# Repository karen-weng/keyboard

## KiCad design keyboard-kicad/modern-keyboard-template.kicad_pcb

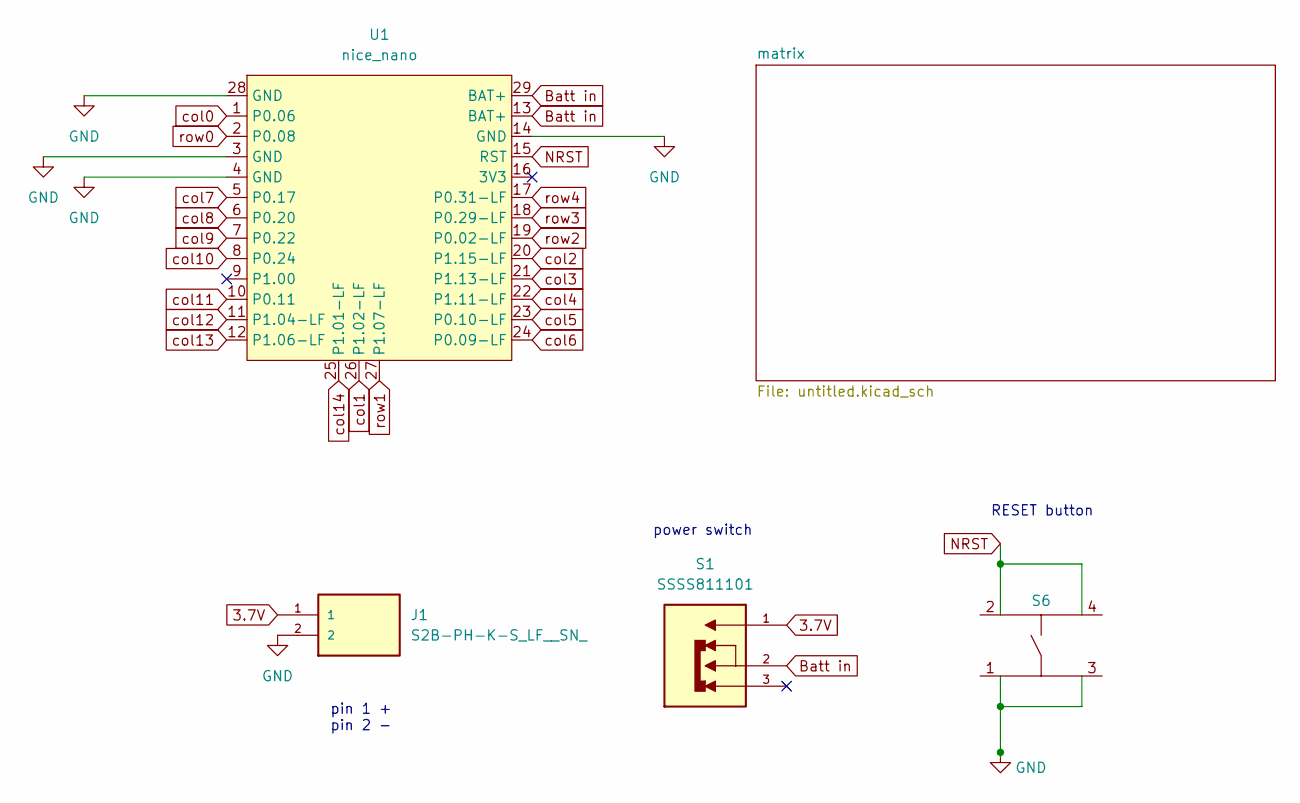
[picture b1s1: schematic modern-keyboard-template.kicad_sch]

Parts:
J1: S2B-PH-K-S_LF__SN_; JST_S2B-PH-K-S_LF__SN_
S1: SSSS811101; SW_SSSS811101; PARTREV N/A
S6: EVQ-PUA02K
U1: nice_nano; nice_nano_AH_USBup

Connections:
3.7V: J1.1, S1.1
Batt in: S1.2, U1.13 (BAT+), U1.29 (BAT+)
GND: J1.2, S6.1, S6.3, U1.3 (GND), U1.4 (GND), U1.14 (GND), U1.28 (GND)
NRST: S6.2, S6.4, U1.15 (RST)
col0: U1.1 (P0.06); also elsewhere on the board
col1: U1.26 (P1.02-LF); also elsewhere on the board
col2: U1.20 (P1.15-LF); also elsewhere on the board
col3: U1.21 (P1.13-LF); also elsewhere on the board
col4: U1.22 (P1.11-LF); also elsewhere on the board
col5: U1.23 (P0.10-LF); also elsewhere on the board
col6: U1.24 (P0.09-LF); also elsewhere on the board
col7: U1.5 (P0.17); also elsewhere on the board
col8: U1.6 (P0.20); also elsewhere on the board
col9: U1.7 (P0.22); also elsewhere on the board
col10: U1.8 (P0.24); also elsewhere on the board
col11: U1.10 (P0.11); also elsewhere on the board
col12: U1.11 (P1.04-LF); also elsewhere on the board
col13: U1.12 (P1.06-LF); also elsewhere on the board
col14: U1.25 (P1.01-LF); also elsewhere on the board
row0: U1.2 (P0.08); also elsewhere on the board
row1: U1.27 (P1.07-LF); also elsewhere on the board
row2: U1.19 (P0.02-LF); also elsewhere on the board
row3: U1.18 (P0.29-LF); also elsewhere on the board
row4: U1.17 (P0.31-LF); also elsewhere on the board

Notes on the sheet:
RESET button
power switch
pin 1 + pin 2 -

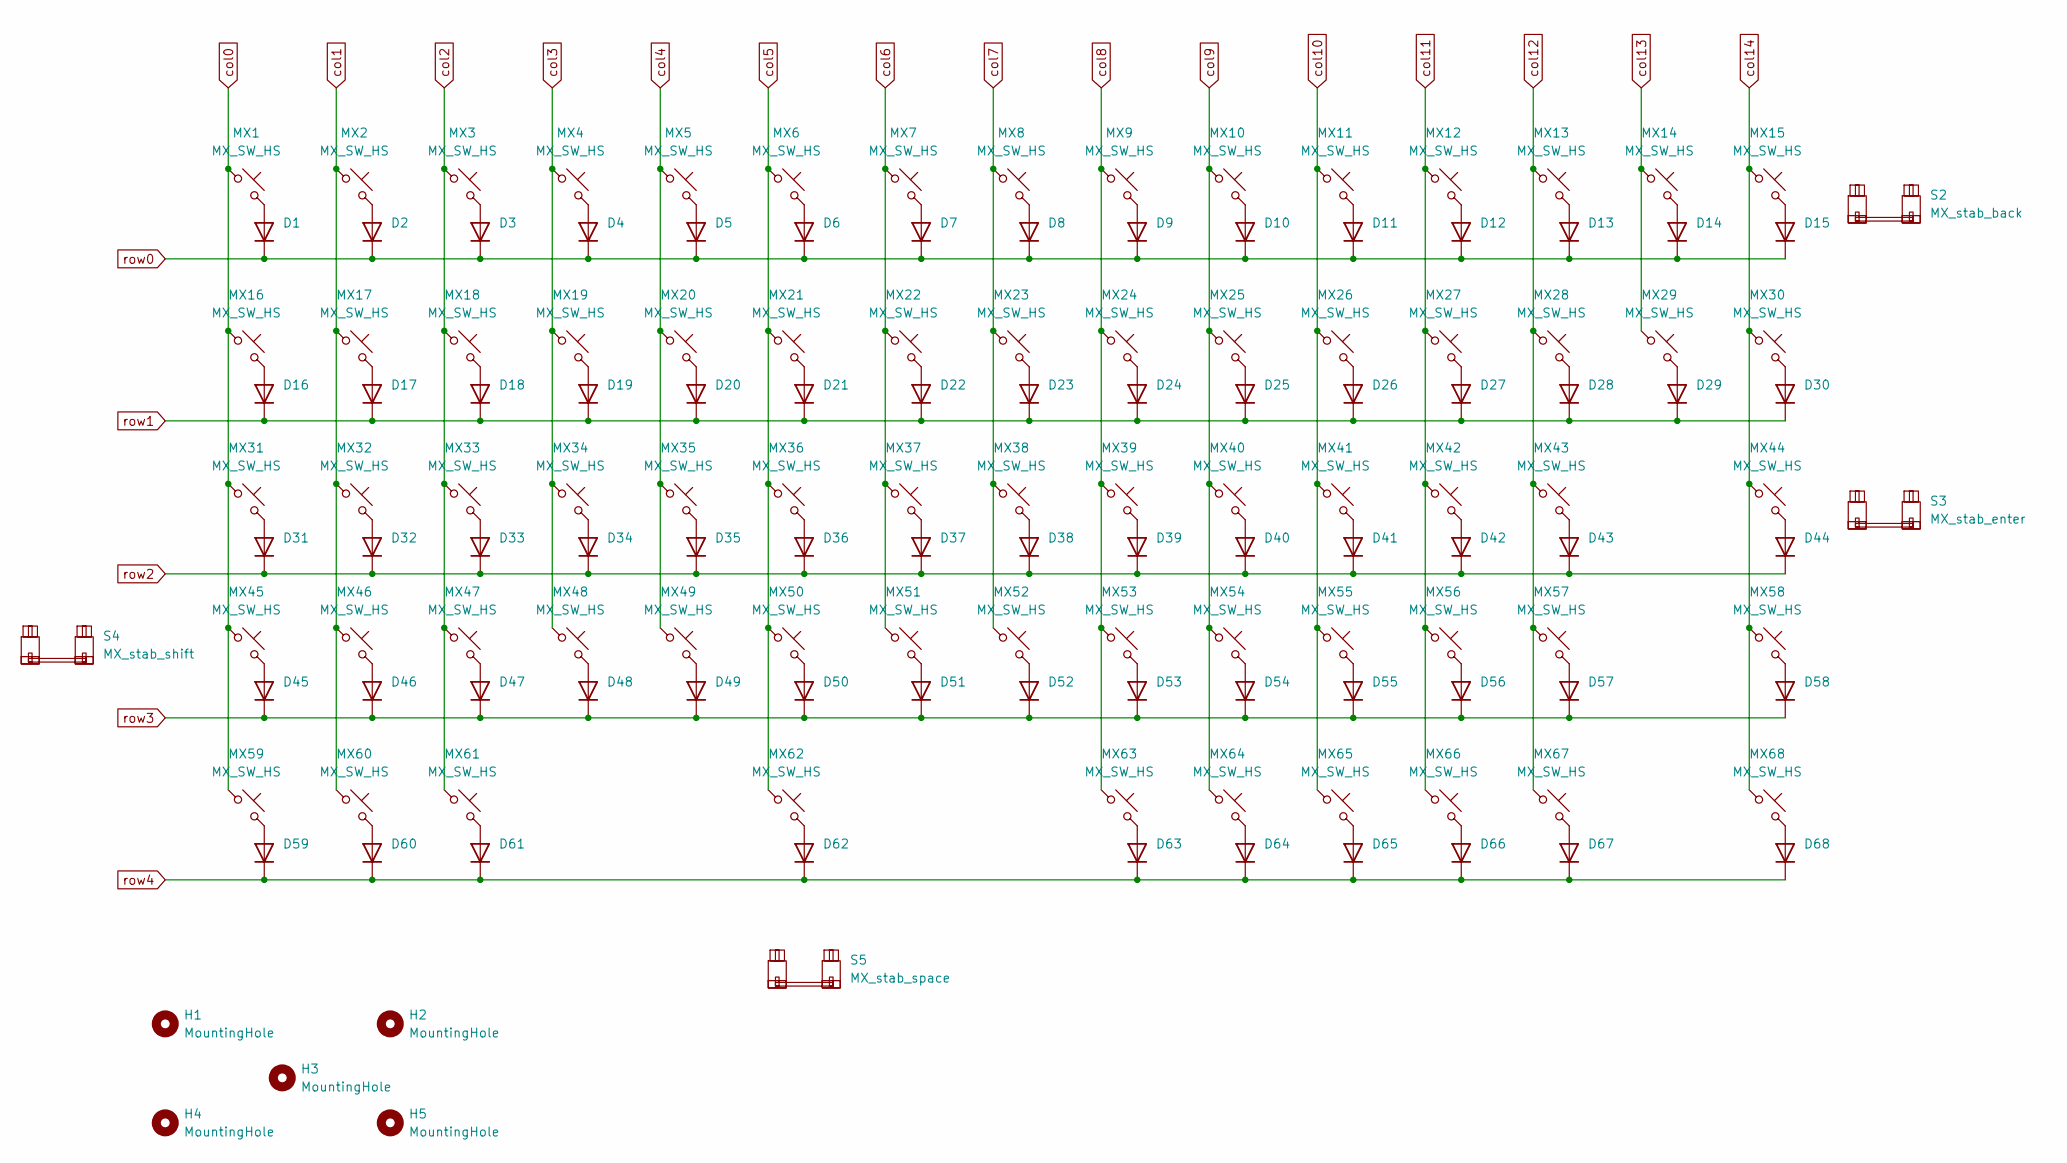
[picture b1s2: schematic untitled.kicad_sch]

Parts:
D1, D2, D3, D4, D5, D6, D7, D8, D9, D10, D11, D12, D13, D14, D15, D16, D17, D18, D19, D20, D21, D22, D23, D24, D25, D26, D27, D28, D29, D30, D31, D32, D33, D34, D35, D36, D37, D38, D39, D40, D41, D42, D43, D44, D45, D46, D47, D48, D49, D50, D51, D52, D53, D54, D55, D56, D57, D58, D59, D60, D61, D62, D63, D64, D65, D66, D67, D68: D; D_SOD-123
H1, H2, H3, H4, H5: MountingHole; MountingHole_2.2mm_M2
MX1, MX2, MX3, MX4, MX5, MX6, MX7, MX8, MX9, MX10, MX11, MX12, MX13, MX14, MX15, MX16, MX17, MX18, MX19, MX20, MX21, MX22, MX23, MX24, MX25, MX26, MX27, MX28, MX29, MX30, MX31, MX32, MX33, MX34, MX35, MX36, MX37, MX38, MX39, MX40, MX41, MX42, MX43, MX44, MX45, MX46, MX47, MX48, MX49, MX50, MX51, MX52, MX53, MX54, MX55, MX56, MX57, MX58, MX59, MX60, MX61, MX62, MX63, MX64, MX65, MX66, MX67, MX68: MX_SW_HS; SW_MX_HS_CPG151101S11_1u
S2: MX_stab_back; STAB_MX_2u
S3: MX_stab_enter; STAB_MX_2.25u
S4: MX_stab_shift; STAB_MX_2.25u
S5: MX_stab_space; STAB_MX_P_6.25u

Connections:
unnamed: D1.2 (A), MX1.2
unnamed: D2.2 (A), MX2.2
unnamed: D3.2 (A), MX3.2
unnamed: D4.2 (A), MX4.2
unnamed: D5.2 (A), MX5.2
unnamed: D6.2 (A), MX6.2
unnamed: D7.2 (A), MX7.2
unnamed: D8.2 (A), MX8.2
unnamed: D9.2 (A), MX9.2
unnamed: D10.2 (A), MX10.2
unnamed: D11.2 (A), MX11.2
unnamed: D12.2 (A), MX12.2
unnamed: D13.2 (A), MX13.2
unnamed: D14.2 (A), MX14.2
unnamed: D15.2 (A), MX15.2
unnamed: D16.2 (A), MX16.2
unnamed: D17.2 (A), MX17.2
unnamed: D18.2 (A), MX18.2
unnamed: D19.2 (A), MX19.2
unnamed: D20.2 (A), MX20.2
unnamed: D21.2 (A), MX21.2
unnamed: D22.2 (A), MX22.2
unnamed: D23.2 (A), MX23.2
unnamed: D24.2 (A), MX24.2
unnamed: D25.2 (A), MX25.2
unnamed: D26.2 (A), MX26.2
unnamed: D27.2 (A), MX27.2
unnamed: D28.2 (A), MX28.2
unnamed: D29.2 (A), MX29.2
unnamed: D30.2 (A), MX30.2
unnamed: D31.2 (A), MX31.2
unnamed: D32.2 (A), MX32.2
unnamed: D33.2 (A), MX33.2
unnamed: D34.2 (A), MX34.2
unnamed: D35.2 (A), MX35.2
unnamed: D36.2 (A), MX36.2
unnamed: D37.2 (A), MX37.2
unnamed: D38.2 (A), MX38.2
unnamed: D39.2 (A), MX39.2
unnamed: D40.2 (A), MX40.2
unnamed: D41.2 (A), MX41.2
unnamed: D42.2 (A), MX42.2
unnamed: D43.2 (A), MX43.2
unnamed: D44.2 (A), MX44.2
unnamed: D45.2 (A), MX45.2
unnamed: D46.2 (A), MX46.2
unnamed: D47.2 (A), MX47.2
unnamed: D48.2 (A), MX48.2
unnamed: D49.2 (A), MX49.2
unnamed: D50.2 (A), MX50.2
unnamed: D51.2 (A), MX51.2
unnamed: D52.2 (A), MX52.2
unnamed: D53.2 (A), MX53.2
unnamed: D54.2 (A), MX54.2
unnamed: D55.2 (A), MX55.2
unnamed: D56.2 (A), MX56.2
unnamed: D57.2 (A), MX57.2
unnamed: D58.2 (A), MX58.2
unnamed: D59.2 (A), MX59.2
unnamed: D60.2 (A), MX60.2
unnamed: D61.2 (A), MX61.2
unnamed: D62.2 (A), MX62.2
unnamed: D63.2 (A), MX63.2
unnamed: D64.2 (A), MX64.2
unnamed: D65.2 (A), MX65.2
unnamed: D66.2 (A), MX66.2
unnamed: D67.2 (A), MX67.2
unnamed: D68.2 (A), MX68.2
col0: MX1.1, MX16.1, MX31.1, MX45.1, MX59.1; also elsewhere on the board
col1: MX2.1, MX17.1, MX32.1, MX46.1, MX60.1; also elsewhere on the board
col2: MX3.1, MX18.1, MX33.1, MX47.1, MX61.1; also elsewhere on the board
col3: MX4.1, MX19.1, MX34.1, MX48.1; also elsewhere on the board
col4: MX5.1, MX20.1, MX35.1, MX49.1; also elsewhere on the board
col5: MX6.1, MX21.1, MX36.1, MX50.1, MX62.1; also elsewhere on the board
col6: MX7.1, MX22.1, MX37.1, MX51.1; also elsewhere on the board
col7: MX8.1, MX23.1, MX38.1, MX52.1; also elsewhere on the board
col8: MX9.1, MX24.1, MX39.1, MX53.1, MX63.1; also elsewhere on the board
col9: MX10.1, MX25.1, MX40.1, MX54.1, MX64.1; also elsewhere on the board
col10: MX11.1, MX26.1, MX41.1, MX55.1, MX65.1; also elsewhere on the board
col11: MX12.1, MX27.1, MX42.1, MX56.1, MX66.1; also elsewhere on the board
col12: MX13.1, MX28.1, MX43.1, MX57.1, MX67.1; also elsewhere on the board
col13: MX14.1, MX29.1; also elsewhere on the board
col14: MX15.1, MX30.1, MX44.1, MX58.1, MX68.1; also elsewhere on the board
row0: D1.1 (K), D2.1 (K), D3.1 (K), D4.1 (K), D5.1 (K), D6.1 (K), D7.1 (K), D8.1 (K), D9.1 (K), D10.1 (K), D11.1 (K), D12.1 (K), D13.1 (K), D14.1 (K), D15.1 (K); also elsewhere on the board
row1: D16.1 (K), D17.1 (K), D18.1 (K), D19.1 (K), D20.1 (K), D21.1 (K), D22.1 (K), D23.1 (K), D24.1 (K), D25.1 (K), D26.1 (K), D27.1 (K), D28.1 (K), D29.1 (K), D30.1 (K); also elsewhere on the board
row2: D31.1 (K), D32.1 (K), D33.1 (K), D34.1 (K), D35.1 (K), D36.1 (K), D37.1 (K), D38.1 (K), D39.1 (K), D40.1 (K), D41.1 (K), D42.1 (K), D43.1 (K), D44.1 (K); also elsewhere on the board
row3: D45.1 (K), D46.1 (K), D47.1 (K), D48.1 (K), D49.1 (K), D50.1 (K), D51.1 (K), D52.1 (K), D53.1 (K), D54.1 (K), D55.1 (K), D56.1 (K), D57.1 (K), D58.1 (K); also elsewhere on the board
row4: D59.1 (K), D60.1 (K), D61.1 (K), D62.1 (K), D63.1 (K), D64.1 (K), D65.1 (K), D66.1 (K), D67.1 (K), D68.1 (K); also elsewhere on the board

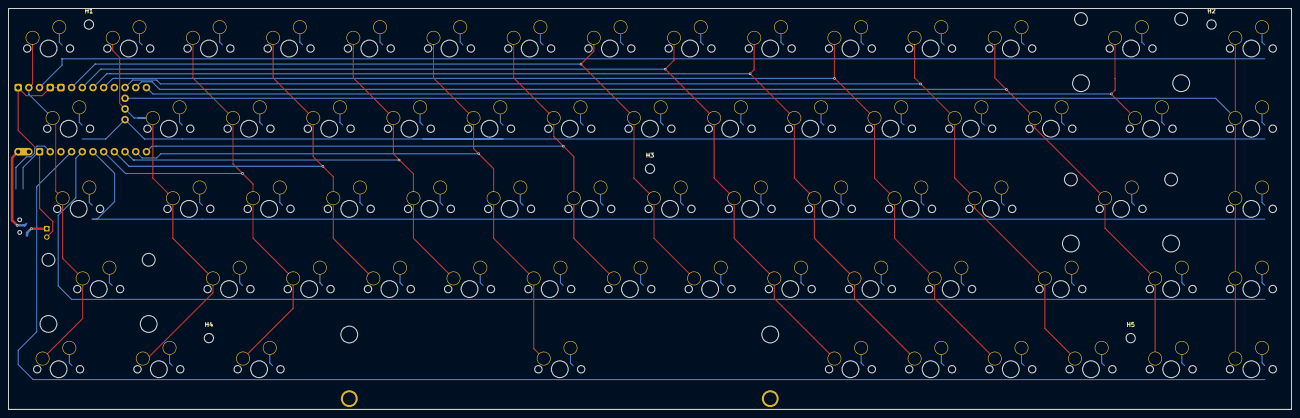
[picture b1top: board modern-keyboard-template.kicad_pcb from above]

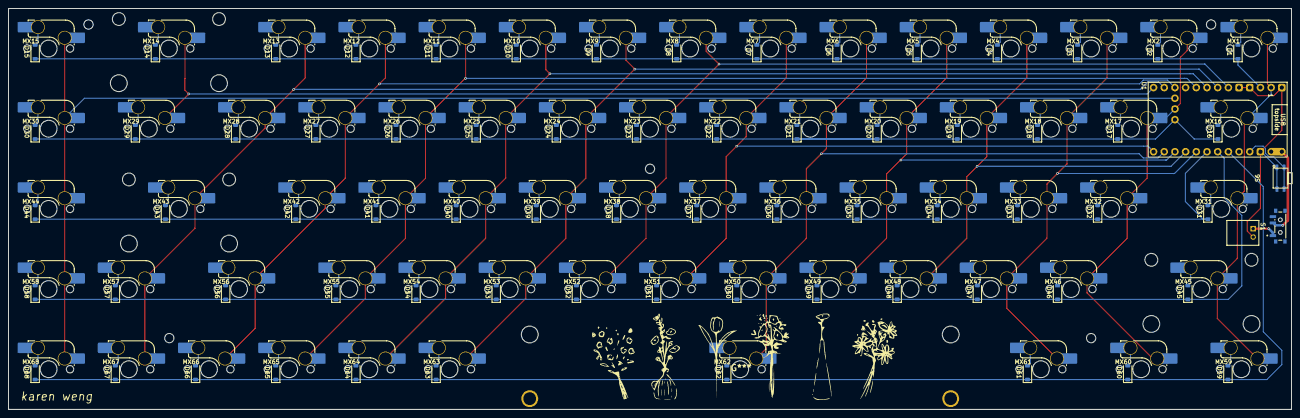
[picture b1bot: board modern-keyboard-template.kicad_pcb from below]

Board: 2 copper layers, 304.8 x 95.2 mm, 149 parts (140 on the bottom side), 92 nets.

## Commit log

2025-06-08 no func keys
2025-07-28 kicad for keyboard
2025-07-28 updated keyboard
2025-07-28 pcb larger outline
2025-07-29 added flower image
2025-08-01 final kicad
